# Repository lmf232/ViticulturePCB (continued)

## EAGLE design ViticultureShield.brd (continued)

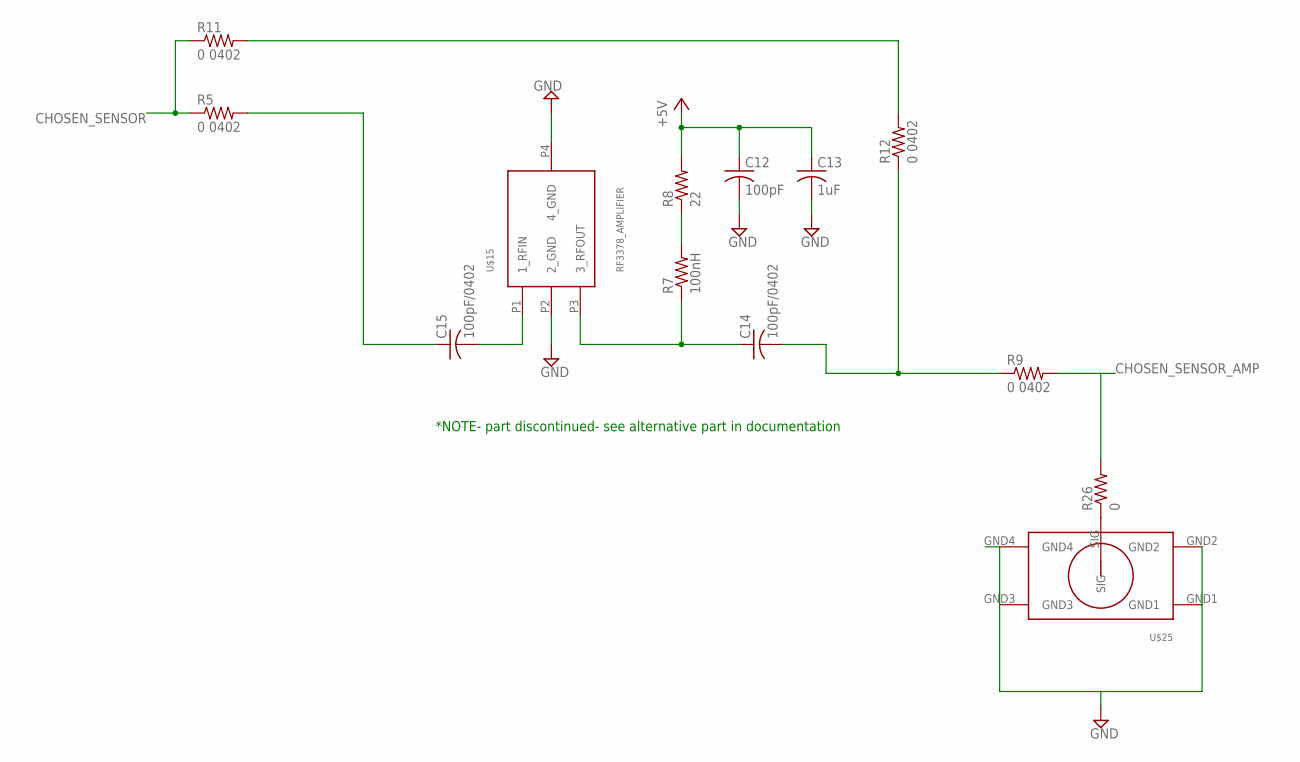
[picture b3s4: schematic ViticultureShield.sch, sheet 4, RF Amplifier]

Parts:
C12: 100pF; C0603
C13: 1uF; C0603
C14, C15: 100pF/0402; C0402
R5, R9, R11, R12: 0 0402; R0402
R7: 100nH; R0603
R8: 22; R0805
R26: 0; R0603
U$15: RF3378_AMPLIFIER; TO243AA/SOT89
U$25: MINISMP_PE44970_THRUHOLE; MINISMP_PE44970_THRU_HOLE

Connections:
+5V: C12.1, C13.1, R8.2; also elsewhere on the board
CHOSEN_SENSOR: R5.1, R11.1; also elsewhere on the board
CHOSEN_SENSOR_AMP: R9.2, R26.2
GND: C12.2, C13.2, U$15.P2 (2_GND), U$15.P4 (4_GND), U$25.GND1, U$25.GND2, U$25.GND3; also elsewhere on the board
unnamed: C14.1, R7.1, U$15.P3 (3_RFOUT)
unnamed: R7.2, R8.1
unnamed: C15.2, U$15.P1 (1_RFIN)
unnamed: C14.2, R9.1, R12.1
unnamed: C15.1, R5.2
unnamed: R11.2, R12.2
unnamed: R26.1, U$25.SIG

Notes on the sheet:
*NOTE- part discontinued- see alternative part in documentation

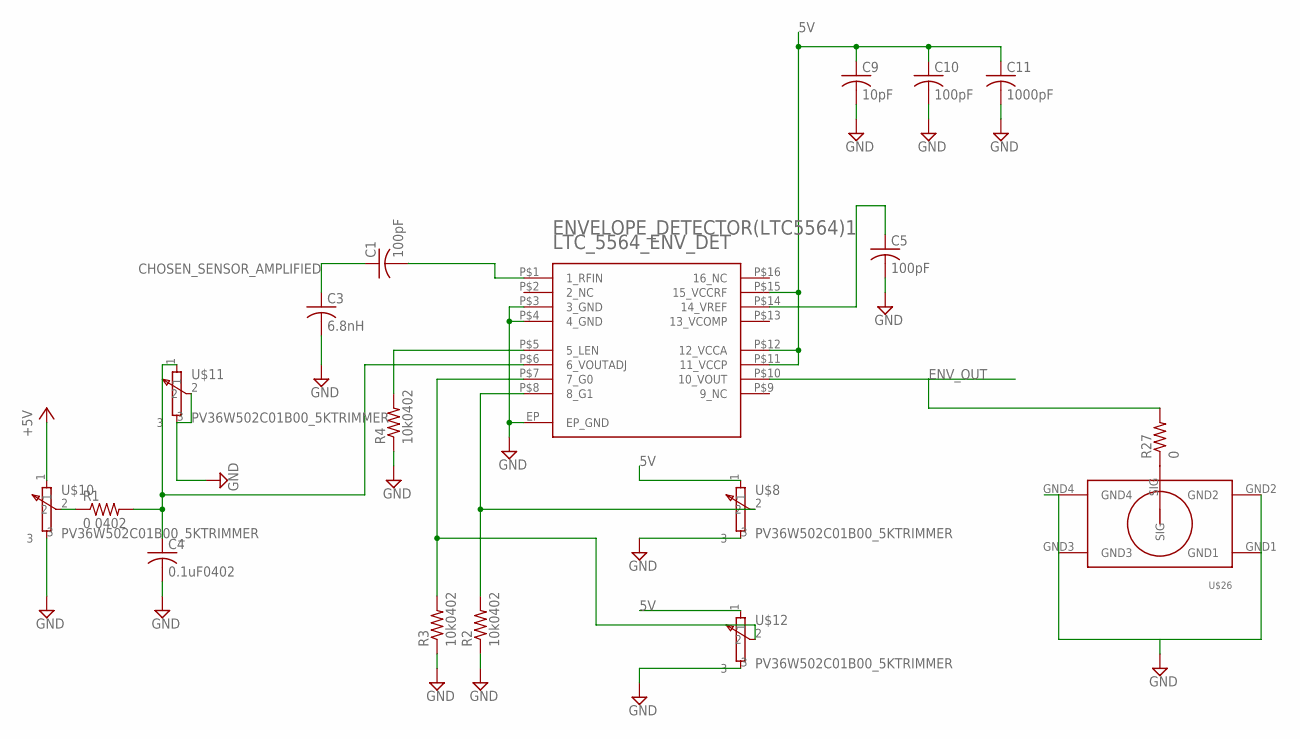
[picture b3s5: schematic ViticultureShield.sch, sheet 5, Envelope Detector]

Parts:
C1, C5, C10: 100pF; C0402
C3: 6.8nH; C0402
C4: 0.1uF0402; C0402
C9: 10pF; C0402
C11: 1000pF; C0402
ENVELOPE_DETECTOR(LTC5564)1: LTC_5564_ENV_DET; QFN16
R1: 0 0402; R0402
R2, R3, R4: 10k0402; R0402
R27: 0; R0603
U$8, U$10, U$11, U$12: PV36W502C01B00_5KTRIMMER
U$26: MINISMP_PE44970_THRUHOLE; MINISMP_PE44970_THRU_HOLE

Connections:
5V: U$8.1, U$12.1; also elsewhere on the board
+5V: U$10.1; also elsewhere on the board
CHOSEN_SENSOR_AMPLIFIED: C1.1, C3.1
ENV_OUT: ENVELOPE_DETECTOR(LTC5564)1.P$10 (10_VOUT), R27.2; also elsewhere on the board
GND: C3.2, C4.2, C5.2, C9.2, C10.2, C11.2, ENVELOPE_DETECTOR(LTC5564)1.EP (EP_GND), ENVELOPE_DETECTOR(LTC5564)1.P$3 (3_GND), ENVELOPE_DETECTOR(LTC5564)1.P$4 (4_GND), R2.1, R3.1, R4.1, U$8.3, U$10.3, U$12.3, U$26.GND1, U$26.GND2, U$26.GND3; also elsewhere on the board
unnamed: C1.2, ENVELOPE_DETECTOR(LTC5564)1.P$1 (1_RFIN)
unnamed: C4.1, ENVELOPE_DETECTOR(LTC5564)1.P$6 (6_VOUTADJ), R1.2, U$11.1
unnamed: R1.1, U$10.2
unnamed: C5.1, ENVELOPE_DETECTOR(LTC5564)1.P$14 (14_VREF)
unnamed: ENVELOPE_DETECTOR(LTC5564)1.P$8 (8_G1), R2.2, U$8.2
unnamed: ENVELOPE_DETECTOR(LTC5564)1.P$7 (7_G0), R3.2, U$12.2
unnamed: ENVELOPE_DETECTOR(LTC5564)1.P$5 (5_LEN), R4.2
unnamed: U$11.2, U$11.3
unnamed: C9.1, C10.1, C11.1, ENVELOPE_DETECTOR(LTC5564)1.P$11 (11_VCCP), ENVELOPE_DETECTOR(LTC5564)1.P$12 (12_VCCA), ENVELOPE_DETECTOR(LTC5564)1.P$15 (15_VCCRF)
unnamed: R27.1, U$26.SIG

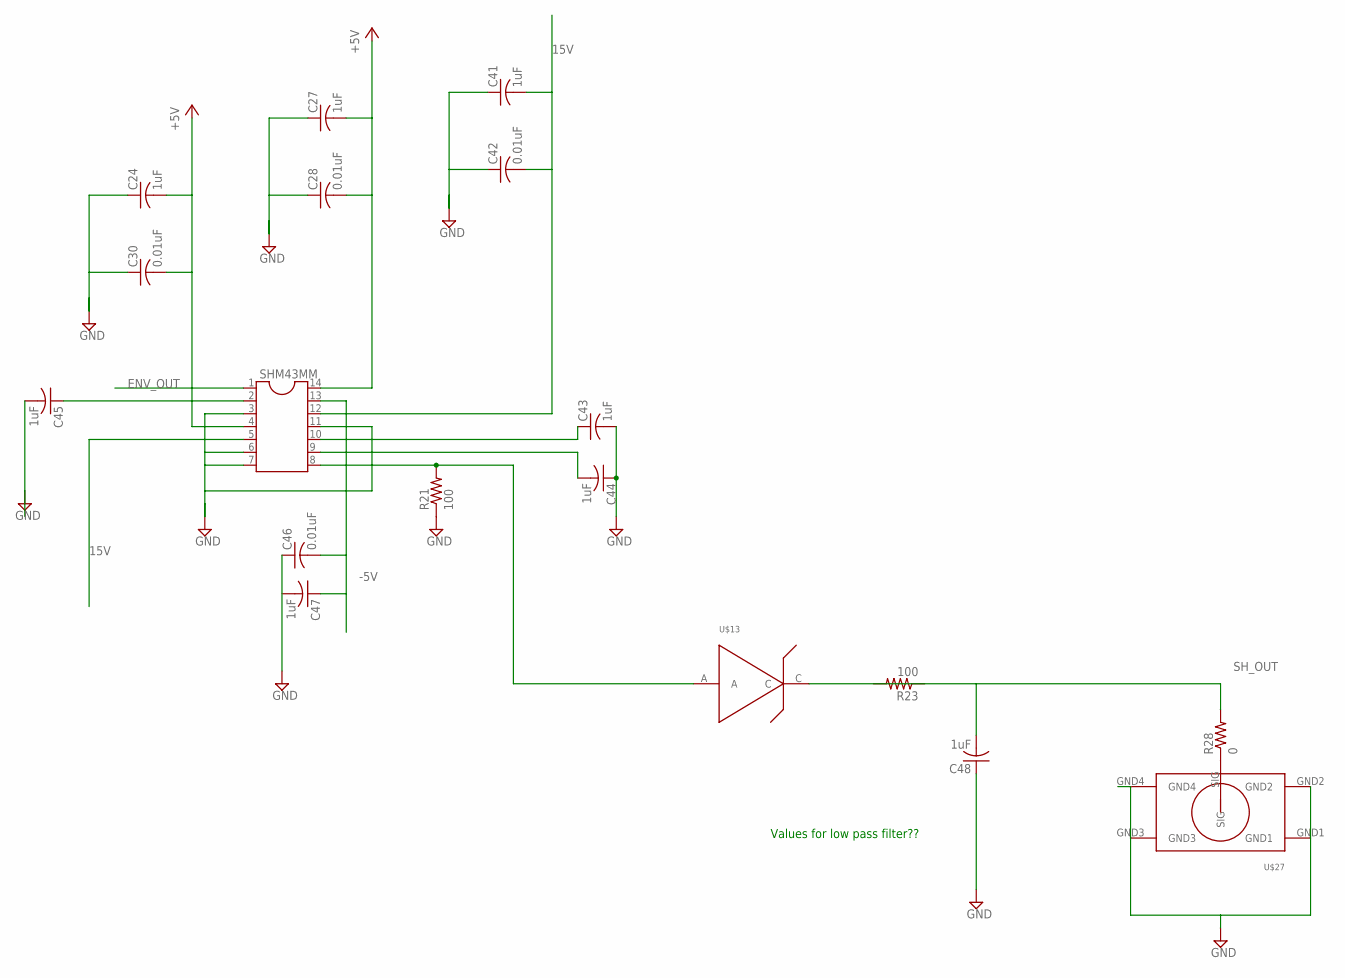
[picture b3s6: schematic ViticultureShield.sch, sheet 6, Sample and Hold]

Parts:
C24, C27, C41, C43, C44, C45, C47, C48: 1uF; C0402
C28, C30, C42, C46: 0.01uF; C0402
R21, R23: 100; R0603
R28: 0; R0603
SHM43MM: DIL14
U$13: ZENER_MMSZ4689-TP; SOD123
U$27: MINISMP_PE44970_THRUHOLE; MINISMP_PE44970_THRU_HOLE

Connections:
5V: C24.2, C27.2, C28.2, C30.2, SHM43MM.4, SHM43MM.14; also elsewhere on the board
15V: C41.2, C42.2, SHM43MM.5, SHM43MM.12; also elsewhere on the board
-5V: C46.2, C47.1, SHM43MM.13; also elsewhere on the board
ENV_OUT: SHM43MM.1; also elsewhere on the board
GND: C24.1, C27.1, C28.1, C30.1, C41.1, C42.1, C43.2, C44.1, C45.2, R21.1, SHM43MM.3, SHM43MM.6, SHM43MM.7, SHM43MM.11, U$27.GND1, U$27.GND2, U$27.GND3; also elsewhere on the board
unnamed: C43.1, SHM43MM.10
unnamed: C44.2, SHM43MM.9
unnamed: C45.1, SHM43MM.2
unnamed: R28.1, U$27.SIG
SAH_OUTPUT: R21.2, SHM43MM.8, U$13.A
SH_OUT: C48.2, R28.2, U$13.C; also elsewhere on the board

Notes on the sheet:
Values for low pass filter??

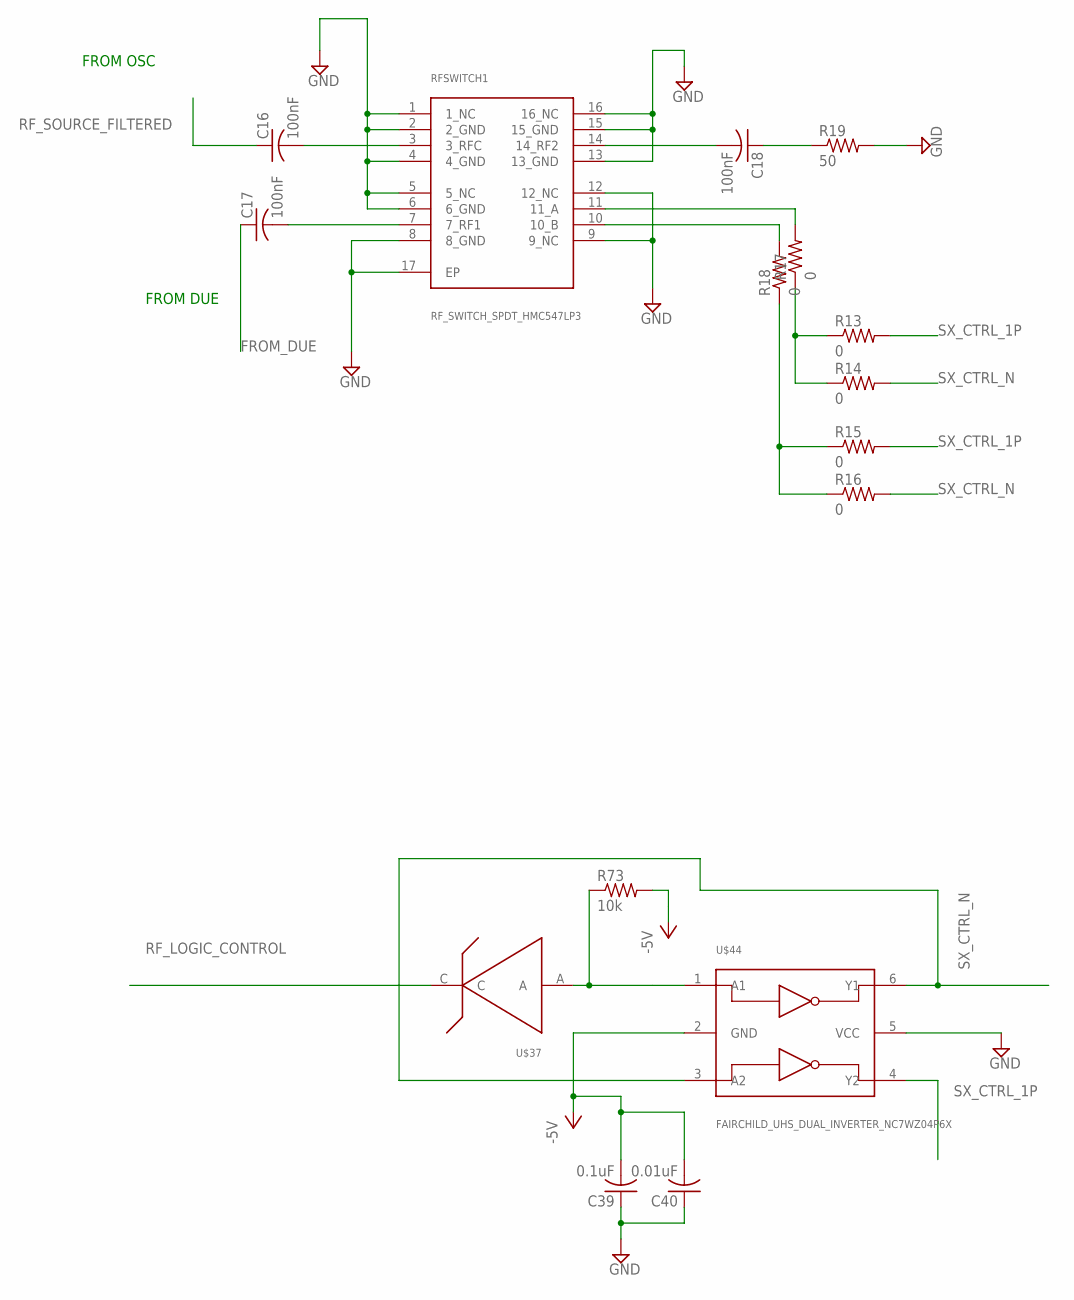
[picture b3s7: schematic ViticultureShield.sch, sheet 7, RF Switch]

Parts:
C16, C17, C18: 100nF; C0603
C39: 0.1uF; C0603
C40: 0.01uF; C0603
R13, R14, R15, R16, R17, R18: 0; R0603
R19: 50; R0603
R73: 10k; R0603
RFSWITCH1: RF_SWITCH_SPDT_HMC547LP3; CP_16_3
U$37: ZENER_MMSZ4689-TP; SOD123
U$44: FAIRCHILD_UHS_DUAL_INVERTER_NC7WZ04P6X; FAIRCHILD_DUAL_INVERTER_NC7WZ04P6X

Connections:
-5V: C39.2, C40.2, R73.2, U$44.2 (GND); also elsewhere on the board
FROM_DUE: C17.1
GND: C39.1, C40.1, R19.2, RFSWITCH1.1 (1_NC), RFSWITCH1.2 (2_GND), RFSWITCH1.4 (4_GND), RFSWITCH1.5 (5_NC), RFSWITCH1.6 (6_GND), RFSWITCH1.8 (8_GND), RFSWITCH1.9 (9_NC), RFSWITCH1.12 (12_NC), RFSWITCH1.13 (13_GND), RFSWITCH1.15 (15_GND), RFSWITCH1.16 (16_NC), RFSWITCH1.17 (EP), U$44.5 (VCC); also elsewhere on the board
unnamed: C16.2, RFSWITCH1.3 (3_RFC)
unnamed: C17.2, RFSWITCH1.7 (7_RF1)
unnamed: R73.1, U$37.A, U$44.1 (A1)
unnamed: C18.2, RFSWITCH1.14 (14_RF2)
unnamed: R17.2, RFSWITCH1.11 (11_A)
unnamed: R15.1, R16.1, R18.1
unnamed: R18.2, RFSWITCH1.10 (10_B)
unnamed: R13.1, R14.1, R17.1
unnamed: C18.1, R19.1
RF_LOGIC_CONTROL: U$37.C; also elsewhere on the board
RF_SOURCE_FILTERED: C16.1; also elsewhere on the board
SX_CTRL_1P: R13.2, R15.2, U$44.4 (Y2)
SX_CTRL_N: R14.2, R16.2, U$44.3 (A2), U$44.6 (Y1)

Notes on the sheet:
FROM OSC
FROM DUE

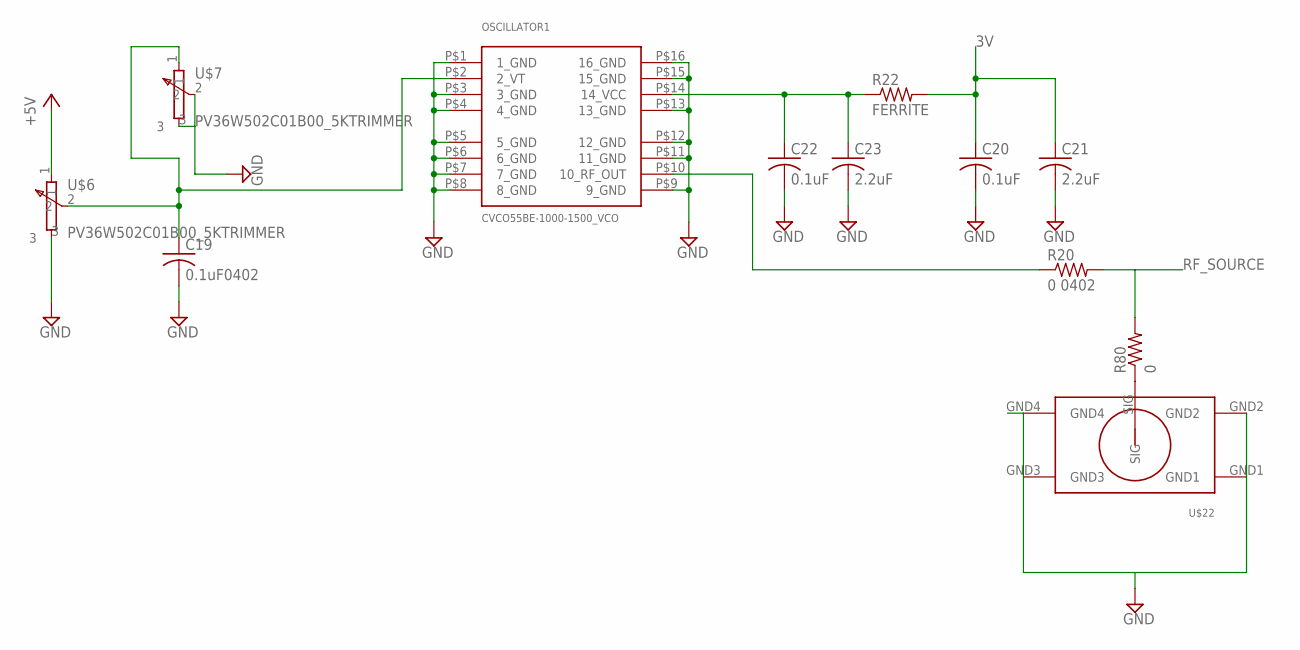
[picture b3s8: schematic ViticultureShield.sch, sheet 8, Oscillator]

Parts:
C19: 0.1uF0402; C0402
C20, C22: 0.1uF; C0603
C21, C23: 2.2uF; C0603
OSCILLATOR1: CVCO55BE-1000-1500_VCO
R20: 0 0402; R0402
R22: FERRITE; R0603
R80: 0; R0603
U$6, U$7: PV36W502C01B00_5KTRIMMER
U$22: MINISMP_PE44970_THRUHOLE; MINISMP_PE44970_THRU_HOLE

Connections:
3V: C20.1, C21.1, R22.2; also elsewhere on the board
5V: U$6.1; also elsewhere on the board
GND: C19.2, C20.2, C21.2, C22.2, C23.2, OSCILLATOR1.P$1 (1_GND), OSCILLATOR1.P$3 (3_GND), OSCILLATOR1.P$4 (4_GND), OSCILLATOR1.P$5 (5_GND), OSCILLATOR1.P$6 (6_GND), OSCILLATOR1.P$7 (7_GND), OSCILLATOR1.P$8 (8_GND), OSCILLATOR1.P$9 (9_GND), OSCILLATOR1.P$11 (11_GND), OSCILLATOR1.P$12 (12_GND), OSCILLATOR1.P$13 (13_GND), OSCILLATOR1.P$15 (15_GND), OSCILLATOR1.P$16 (16_GND), U$6.3, U$7.2, U$7.3, U$22.GND1, U$22.GND2, U$22.GND3; also elsewhere on the board
unnamed: C19.1, OSCILLATOR1.P$2 (2_VT), U$6.2, U$7.1
unnamed: OSCILLATOR1.P$10 (10_RF_OUT), R20.1
unnamed: C22.1, C23.1, OSCILLATOR1.P$14 (14_VCC), R22.1
unnamed: R80.1, U$22.SIG
RF_SOURCE: R20.2, R80.2; also elsewhere on the board

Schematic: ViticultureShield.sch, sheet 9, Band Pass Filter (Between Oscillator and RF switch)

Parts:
C25: 100nF; C0603
C26: 1nF; C0603
R6: 1mohm; R1206
R10: 100mohm; R1206
R24: 0; R0603
U$23: MINISMP_PE44970_THRUHOLE; MINISMP_PE44970_THRU_HOLE

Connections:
GND: C26.1, R6.1, U$23.GND1, U$23.GND2, U$23.GND3; also elsewhere on the board
unnamed: R24.1, U$23.SIG
RF_SOURCE: C25.1, R6.2, R10.1; also elsewhere on the board
RF_SOURCE_FILTERED: C26.2, R10.2, R24.2; also elsewhere on the board

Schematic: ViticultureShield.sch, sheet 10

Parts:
U$16: ZRAY_TEST_1

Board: 4 copper layers, 123 parts (0 on the bottom side), 69 nets, no tracks yet.

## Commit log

2018-03-26 Viticulture PCB Shield
2018-03-26 ViticulturePCB Power Board
2018-03-26 Mamdouhs Files
2018-03-26 Darias Due Code
